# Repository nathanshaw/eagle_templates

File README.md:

# eagle_templates
A collection of EAGLE CAD templates to help with the creation of projects.

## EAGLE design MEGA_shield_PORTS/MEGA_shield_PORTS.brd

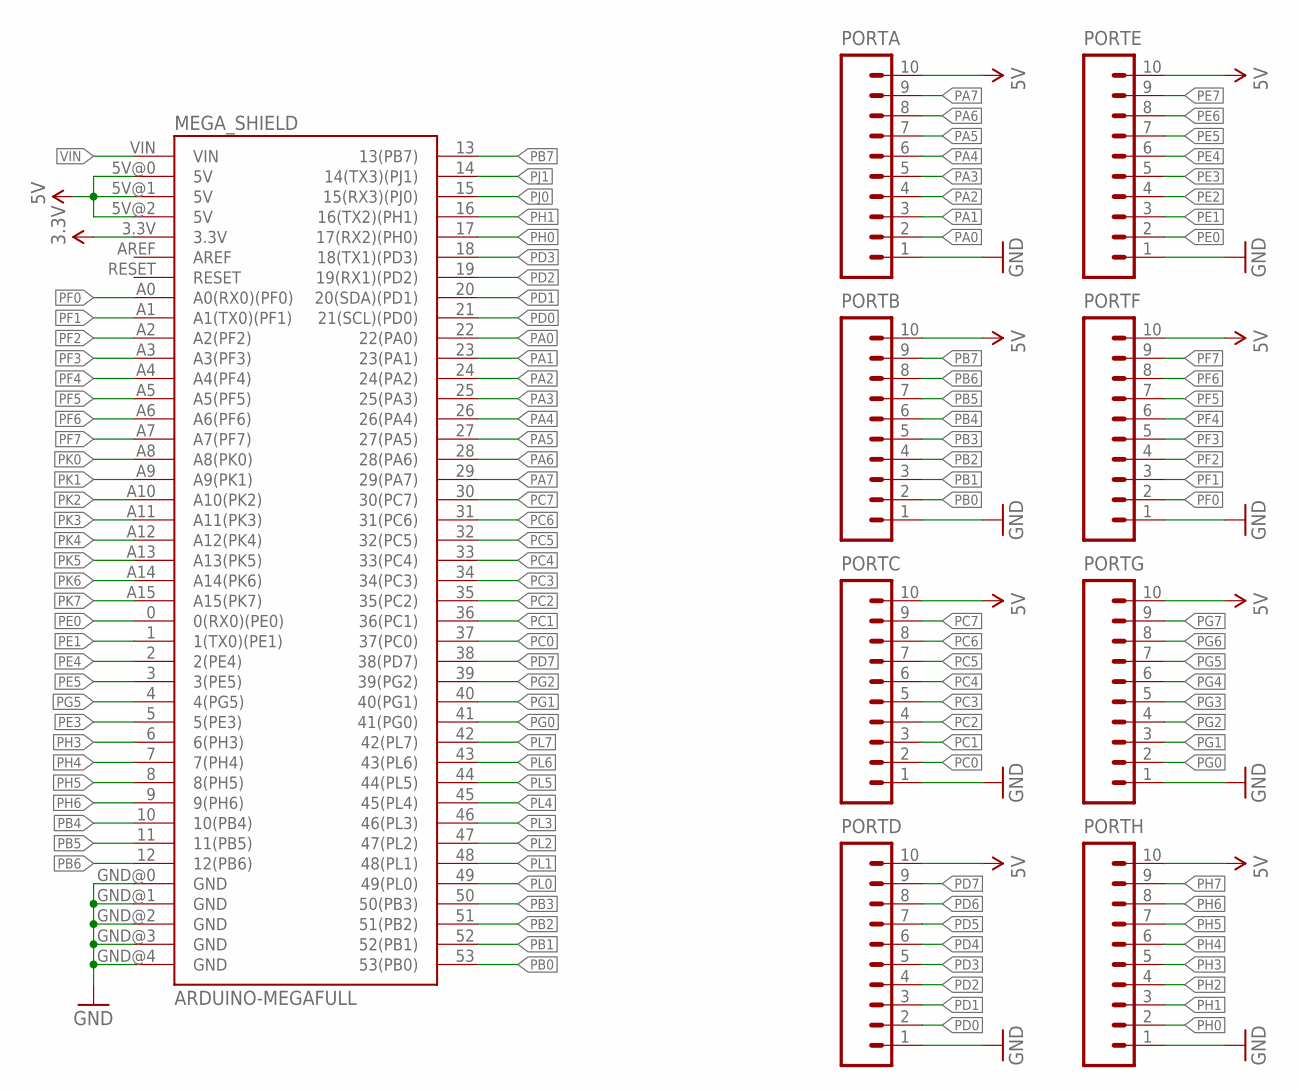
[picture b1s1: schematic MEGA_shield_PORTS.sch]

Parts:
MEGA_SHIELD: ARDUINO-MEGAFULL; ARDUINO_MEGA
PORTA: M10NO_SILK_PTH_FEMALE; 1X10_NO_SILK
PORTB: M10NO_SILK_PTH_FEMALE; 1X10_NO_SILK
PORTC: M10NO_SILK_PTH_FEMALE; 1X10_NO_SILK
PORTD: M10NO_SILK_PTH_FEMALE; 1X10_NO_SILK
PORTE: M10NO_SILK_PTH_FEMALE; 1X10_NO_SILK
PORTF: M10NO_SILK_PTH_FEMALE; 1X10_NO_SILK
PORTG: M10NO_SILK_PTH_FEMALE; 1X10_NO_SILK
PORTH: M10NO_SILK_PTH_FEMALE; 1X10_NO_SILK

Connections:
3.3V: MEGA_SHIELD.3.3V
5V: MEGA_SHIELD.5V@0 (5V), MEGA_SHIELD.5V@1 (5V), MEGA_SHIELD.5V@2 (5V), PORTA.10, PORTB.10, PORTC.10, PORTD.10, PORTE.10, PORTF.10, PORTG.10, PORTH.10
GND: MEGA_SHIELD.GND@0 (GND), MEGA_SHIELD.GND@1 (GND), MEGA_SHIELD.GND@2 (GND), MEGA_SHIELD.GND@3 (GND), MEGA_SHIELD.GND@4 (GND), PORTA.1, PORTB.1, PORTC.1, PORTD.1, PORTE.1, PORTF.1, PORTG.1, PORTH.1
PA0: MEGA_SHIELD.22 (22(PA0)), PORTA.2
PA1: MEGA_SHIELD.23 (23(PA1)), PORTA.3
PA2: MEGA_SHIELD.24 (24(PA2)), PORTA.4
PA3: MEGA_SHIELD.25 (25(PA3)), PORTA.5
PA4: MEGA_SHIELD.26 (26(PA4)), PORTA.6
PA5: MEGA_SHIELD.27 (27(PA5)), PORTA.7
PA6: MEGA_SHIELD.28 (28(PA6)), PORTA.8
PA7: MEGA_SHIELD.29 (29(PA7)), PORTA.9
PB0: MEGA_SHIELD.53 (53(PB0)), PORTB.2
PB1: MEGA_SHIELD.52 (52(PB1)), PORTB.3
PB2: MEGA_SHIELD.51 (51(PB2)), PORTB.4
PB3: MEGA_SHIELD.50 (50(PB3)), PORTB.5
PB4: MEGA_SHIELD.10 (10(PB4)), PORTB.6
PB5: MEGA_SHIELD.11 (11(PB5)), PORTB.7
PB6: MEGA_SHIELD.12 (12(PB6)), PORTB.8
PB7: MEGA_SHIELD.13 (13(PB7)), PORTB.9
PC0: MEGA_SHIELD.37 (37(PC0)), PORTC.2
PC1: MEGA_SHIELD.36 (36(PC1)), PORTC.3
PC2: MEGA_SHIELD.35 (35(PC2)), PORTC.4
PC3: MEGA_SHIELD.34 (34(PC3)), PORTC.5
PC4: MEGA_SHIELD.33 (33(PC4)), PORTC.6
PC5: MEGA_SHIELD.32 (32(PC5)), PORTC.7
PC6: MEGA_SHIELD.31 (31(PC6)), PORTC.8
PC7: MEGA_SHIELD.30 (30(PC7)), PORTC.9
PD0: MEGA_SHIELD.21 (21(SCL)(PD0)), PORTD.2
PD1: MEGA_SHIELD.20 (20(SDA)(PD1)), PORTD.3
PD2: MEGA_SHIELD.19 (19(RX1)(PD2)), PORTD.4
PD3: MEGA_SHIELD.18 (18(TX1)(PD3)), PORTD.5
PD4: PORTD.6
PD5: PORTD.7
PD6: PORTD.8
PD7: MEGA_SHIELD.38 (38(PD7)), PORTD.9
PE0: MEGA_SHIELD.0 (0(RX0)(PE0)), PORTE.2
PE1: MEGA_SHIELD.1 (1(TX0)(PE1)), PORTE.3
PE2: PORTE.4
PE3: MEGA_SHIELD.5 (5(PE3)), PORTE.5
PE4: MEGA_SHIELD.2 (2(PE4)), PORTE.6
PE5: MEGA_SHIELD.3 (3(PE5)), PORTE.7
PE6: PORTE.8
PE7: PORTE.9
PF0: MEGA_SHIELD.A0 (A0(RX0)(PF0)), PORTF.2
PF1: MEGA_SHIELD.A1 (A1(TX0)(PF1)), PORTF.3
PF2: MEGA_SHIELD.A2 (A2(PF2)), PORTF.4
PF3: MEGA_SHIELD.A3 (A3(PF3)), PORTF.5
PF4: MEGA_SHIELD.A4 (A4(PF4)), PORTF.6
PF5: MEGA_SHIELD.A5 (A5(PF5)), PORTF.7
PF6: MEGA_SHIELD.A6 (A6(PF6)), PORTF.8
PF7: MEGA_SHIELD.A7 (A7(PF7)), PORTF.9
PG0: MEGA_SHIELD.41 (41(PG0)), PORTG.2
PG1: MEGA_SHIELD.40 (40(PG1)), PORTG.3
PG2: MEGA_SHIELD.39 (39(PG2)), PORTG.4
PG3: PORTG.5
PG4: PORTG.6
PG5: MEGA_SHIELD.4 (4(PG5)), PORTG.7
PG6: PORTG.8
PG7: PORTG.9
PH0: MEGA_SHIELD.17 (17(RX2)(PH0)), PORTH.2
PH1: MEGA_SHIELD.16 (16(TX2)(PH1)), PORTH.3
PH2: PORTH.4
PH3: MEGA_SHIELD.6 (6(PH3)), PORTH.5
PH4: MEGA_SHIELD.7 (7(PH4)), PORTH.6
PH5: MEGA_SHIELD.8 (8(PH5)), PORTH.7
PH6: MEGA_SHIELD.9 (9(PH6)), PORTH.8
PH7: PORTH.9
PJ0: MEGA_SHIELD.15 (15(RX3)(PJ0))
PJ1: MEGA_SHIELD.14 (14(TX3)(PJ1))
PK0: MEGA_SHIELD.A8 (A8(PK0))
PK1: MEGA_SHIELD.A9 (A9(PK1))
PK2: MEGA_SHIELD.A10 (A10(PK2))
PK3: MEGA_SHIELD.A11 (A11(PK3))
PK4: MEGA_SHIELD.A12 (A12(PK4))
PK5: MEGA_SHIELD.A13 (A13(PK5))
PK6: MEGA_SHIELD.A14 (A14(PK6))
PK7: MEGA_SHIELD.A15 (A15(PK7))
PL0: MEGA_SHIELD.49 (49(PL0))
PL1: MEGA_SHIELD.48 (48(PL1))
PL2: MEGA_SHIELD.47 (47(PL2))
PL3: MEGA_SHIELD.46 (46(PL3))
PL4: MEGA_SHIELD.45 (45(PL4))
PL5: MEGA_SHIELD.44 (44(PL5))
PL6: MEGA_SHIELD.43 (43(PL6))
PL7: MEGA_SHIELD.42 (42(PL7))
VIN: MEGA_SHIELD.VIN

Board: 2 copper layers, 9 parts (0 on the bottom side), 54 nets, no tracks yet.

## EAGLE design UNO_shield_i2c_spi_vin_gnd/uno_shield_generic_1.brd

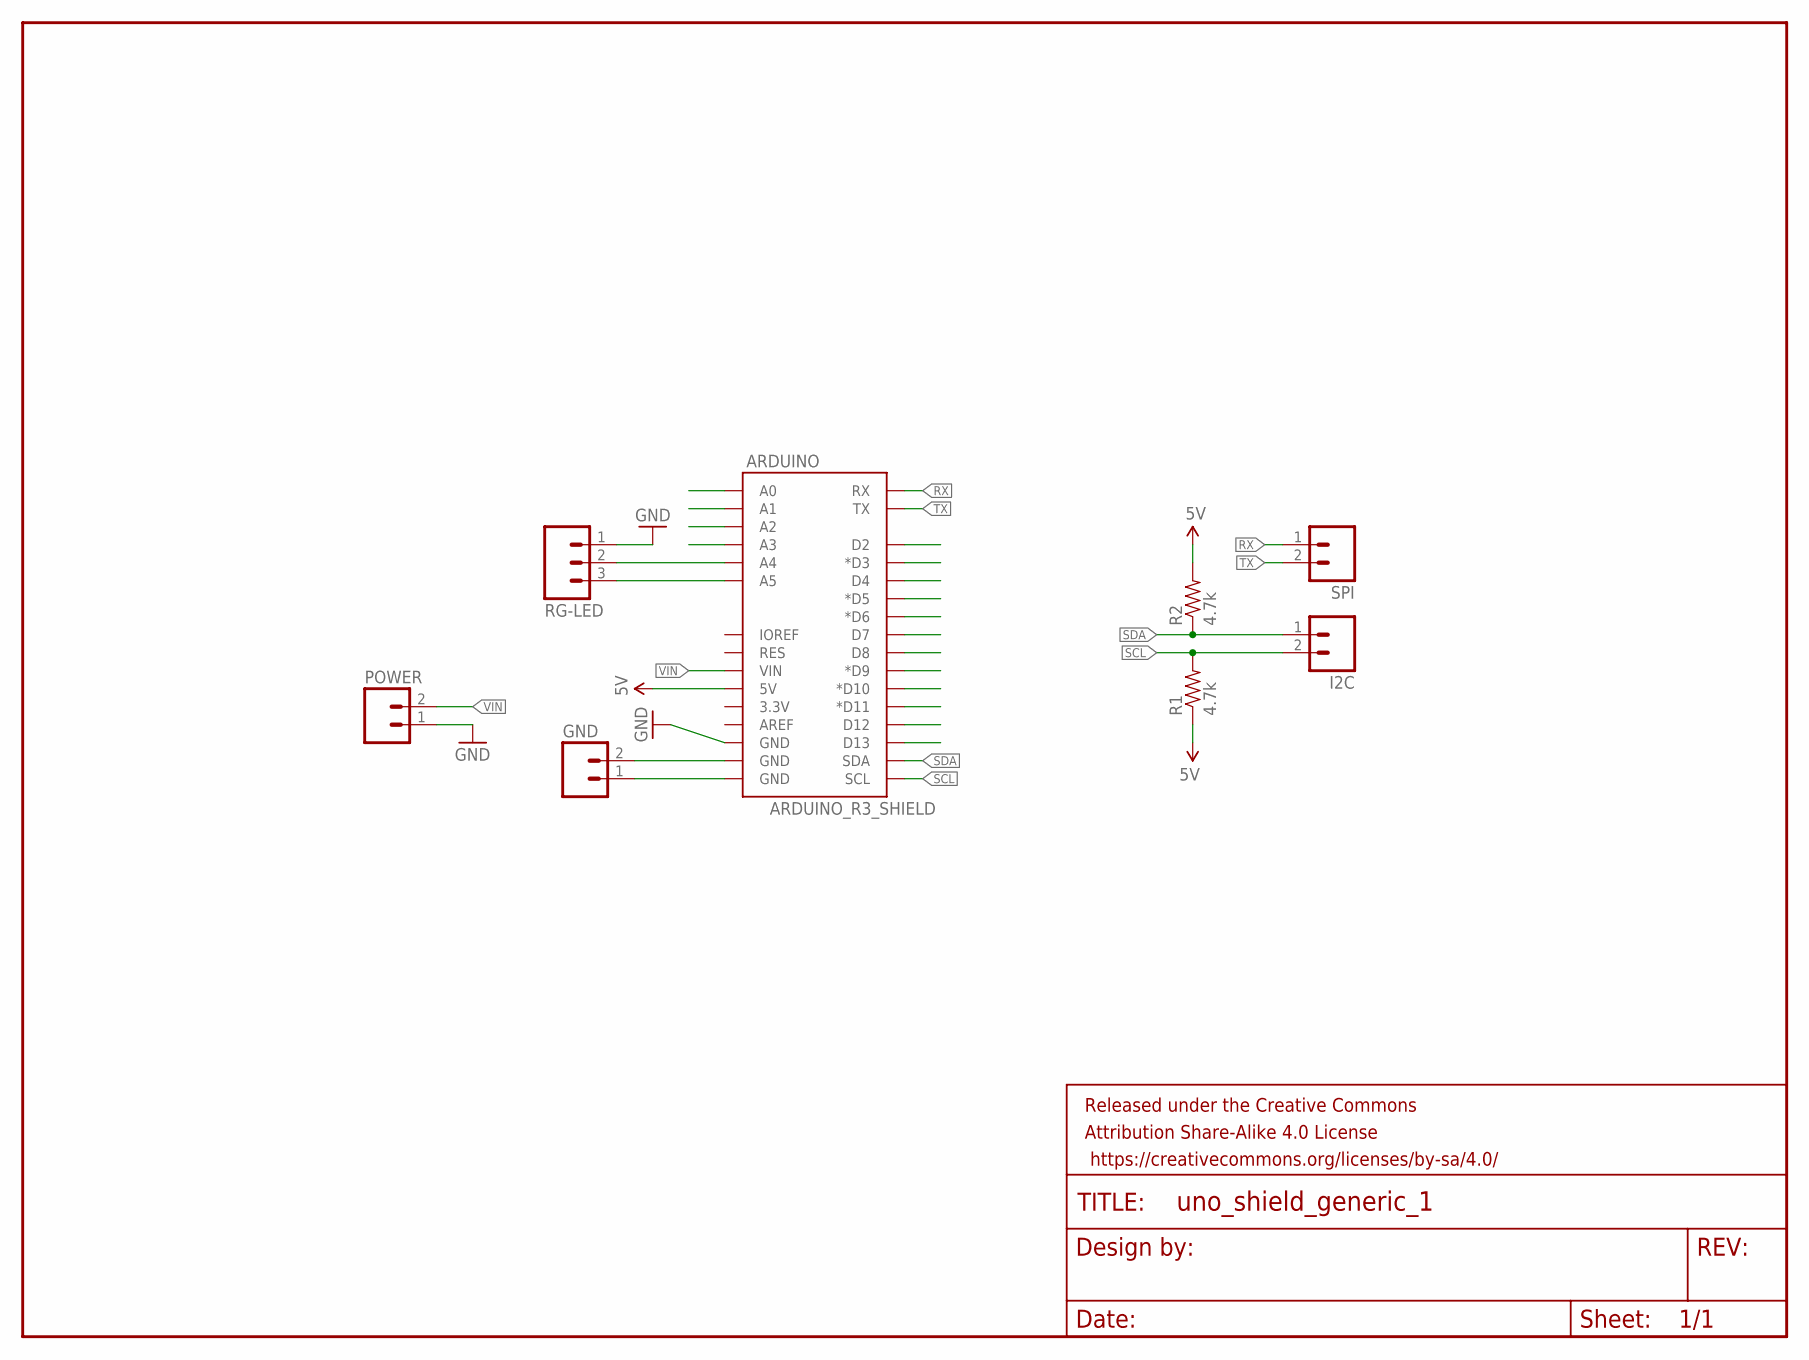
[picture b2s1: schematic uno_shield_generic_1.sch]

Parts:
ARDUINO: ARDUINO_R3_SHIELD; UNO_R3_SHIELD
FRAME1: FRAME-LETTER; CREATIVE_COMMONS
GND: M02LOCK_LONGPADS; 1X02_LOCK_LONGPADS
I2C: M02LOCK_LONGPADS; 1X02_LOCK_LONGPADS
POWER: M02LOCK_LONGPADS; 1X02_LOCK_LONGPADS
R1, R2: 4.7k; AXIAL-0.3-KIT
RG-LED: M03LONGPADS; 1X03_LONGPADS
SPI: M02LOCK_LONGPADS; 1X02_LOCK_LONGPADS

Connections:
5V: ARDUINO.5V, R1.P$1 (1), R2.P$2 (2)
GND: ARDUINO.GND@2 (GND), POWER.1, RG-LED.1
unnamed: ARDUINO.A4, RG-LED.2
unnamed: ARDUINO.A5, RG-LED.3
unnamed: ARDUINO.GND@1 (GND), GND.2
unnamed: ARDUINO.GND@0 (GND), GND.1
RX: ARDUINO.RX, SPI.1
SCL: ARDUINO.SCL, I2C.2, R1.P$2 (2)
SDA: ARDUINO.SDA, I2C.1, R2.P$1 (1)
TX: ARDUINO.TX, SPI.2
VIN: ARDUINO.VIN, POWER.2

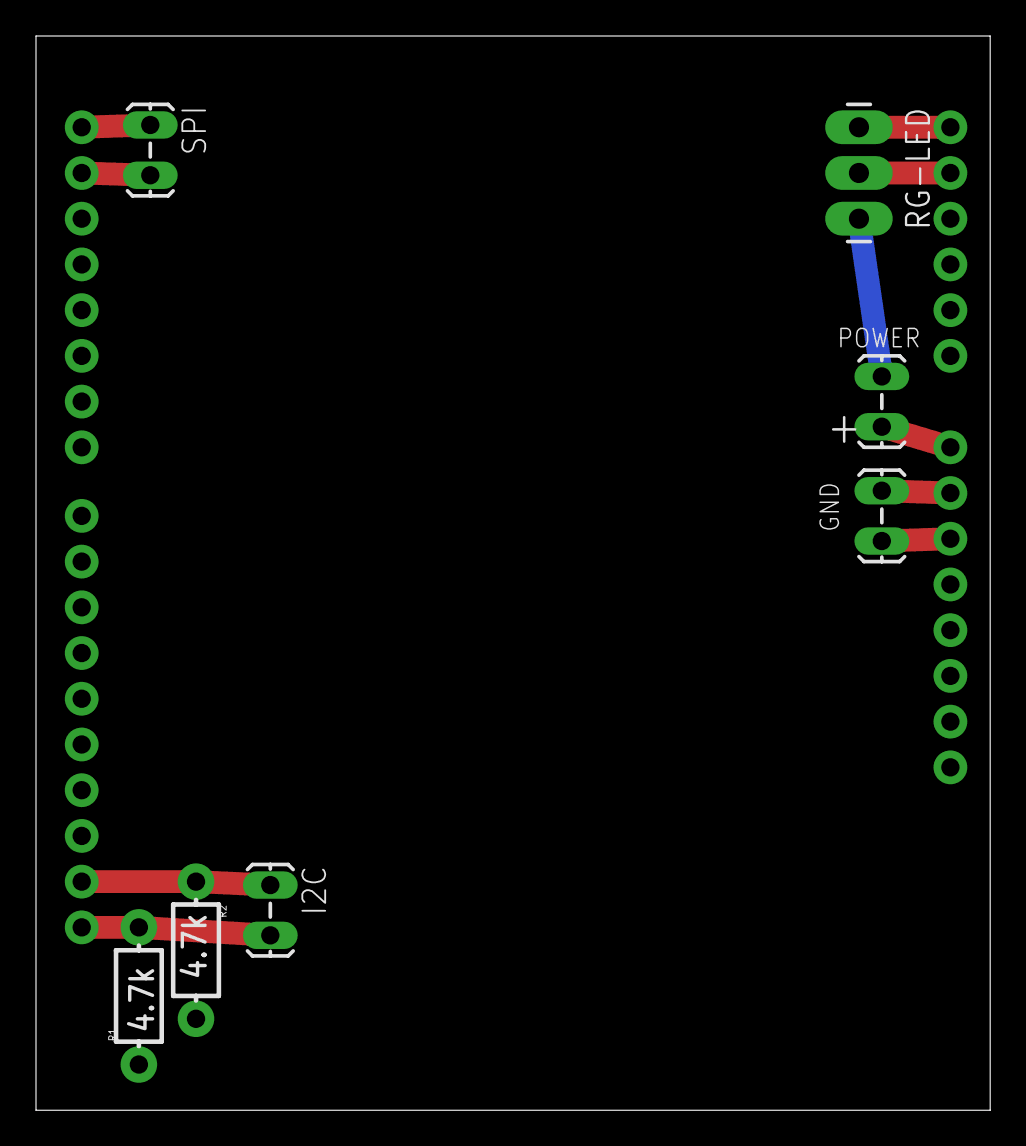
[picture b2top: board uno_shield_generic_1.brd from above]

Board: 2 copper layers, 53.0 x 59.7 mm, 9 parts (0 on the bottom side), 11 nets.

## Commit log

2016-03-21 added templates for the arduino NANO

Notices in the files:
parts and their libraries:
Nathans-Arduinos: Licensing: Creative Commons ShareAlike 4.0 International - https://creativecommons.org/licenses/by-sa/4.0
SparkFun-Aesthetics: Released under the Creative Commons Attribution Share-Alike 4.0 License
SparkFun-Aesthetics: https://creativecommons.org/licenses/by-sa/4.0
